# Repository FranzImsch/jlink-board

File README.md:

# Not A J-Link

Replacement board for the J-Link EDU mini that features a power supply for the target device. It allows you to directly connect a programming probe or proper 2.54mm jumper wires without any adapters and it features a contemporary USB-C port. The chip on the board was carefully removed from a genuine J-Link, so its firmware is still original.

## Partlist

| Name                | Part |
|---------------------|------------|
| C1, C2, C4, C5, C6  | 100nF 0402 |
| C8, C9              | 2.2µF 0402 |
| D1                  | LED 0603 |
| R1, R2              | 5k1 0402 |
| R3, R4              | 33Ω 0402 |
| R7                  | 10k 0402 |
| R8                  | 220Ω 0402 |
| R9 - R13            | 150Ω 0402 |
| U$2                 | TLV75533PDBVR (better: TLV75733PDBVR)        |
| IC1                 | MK22FN128VLH10 (MCU from J-Link) |
| J3                  | 6P Box Header |
| J1                  | USB-C or USB-A plug |

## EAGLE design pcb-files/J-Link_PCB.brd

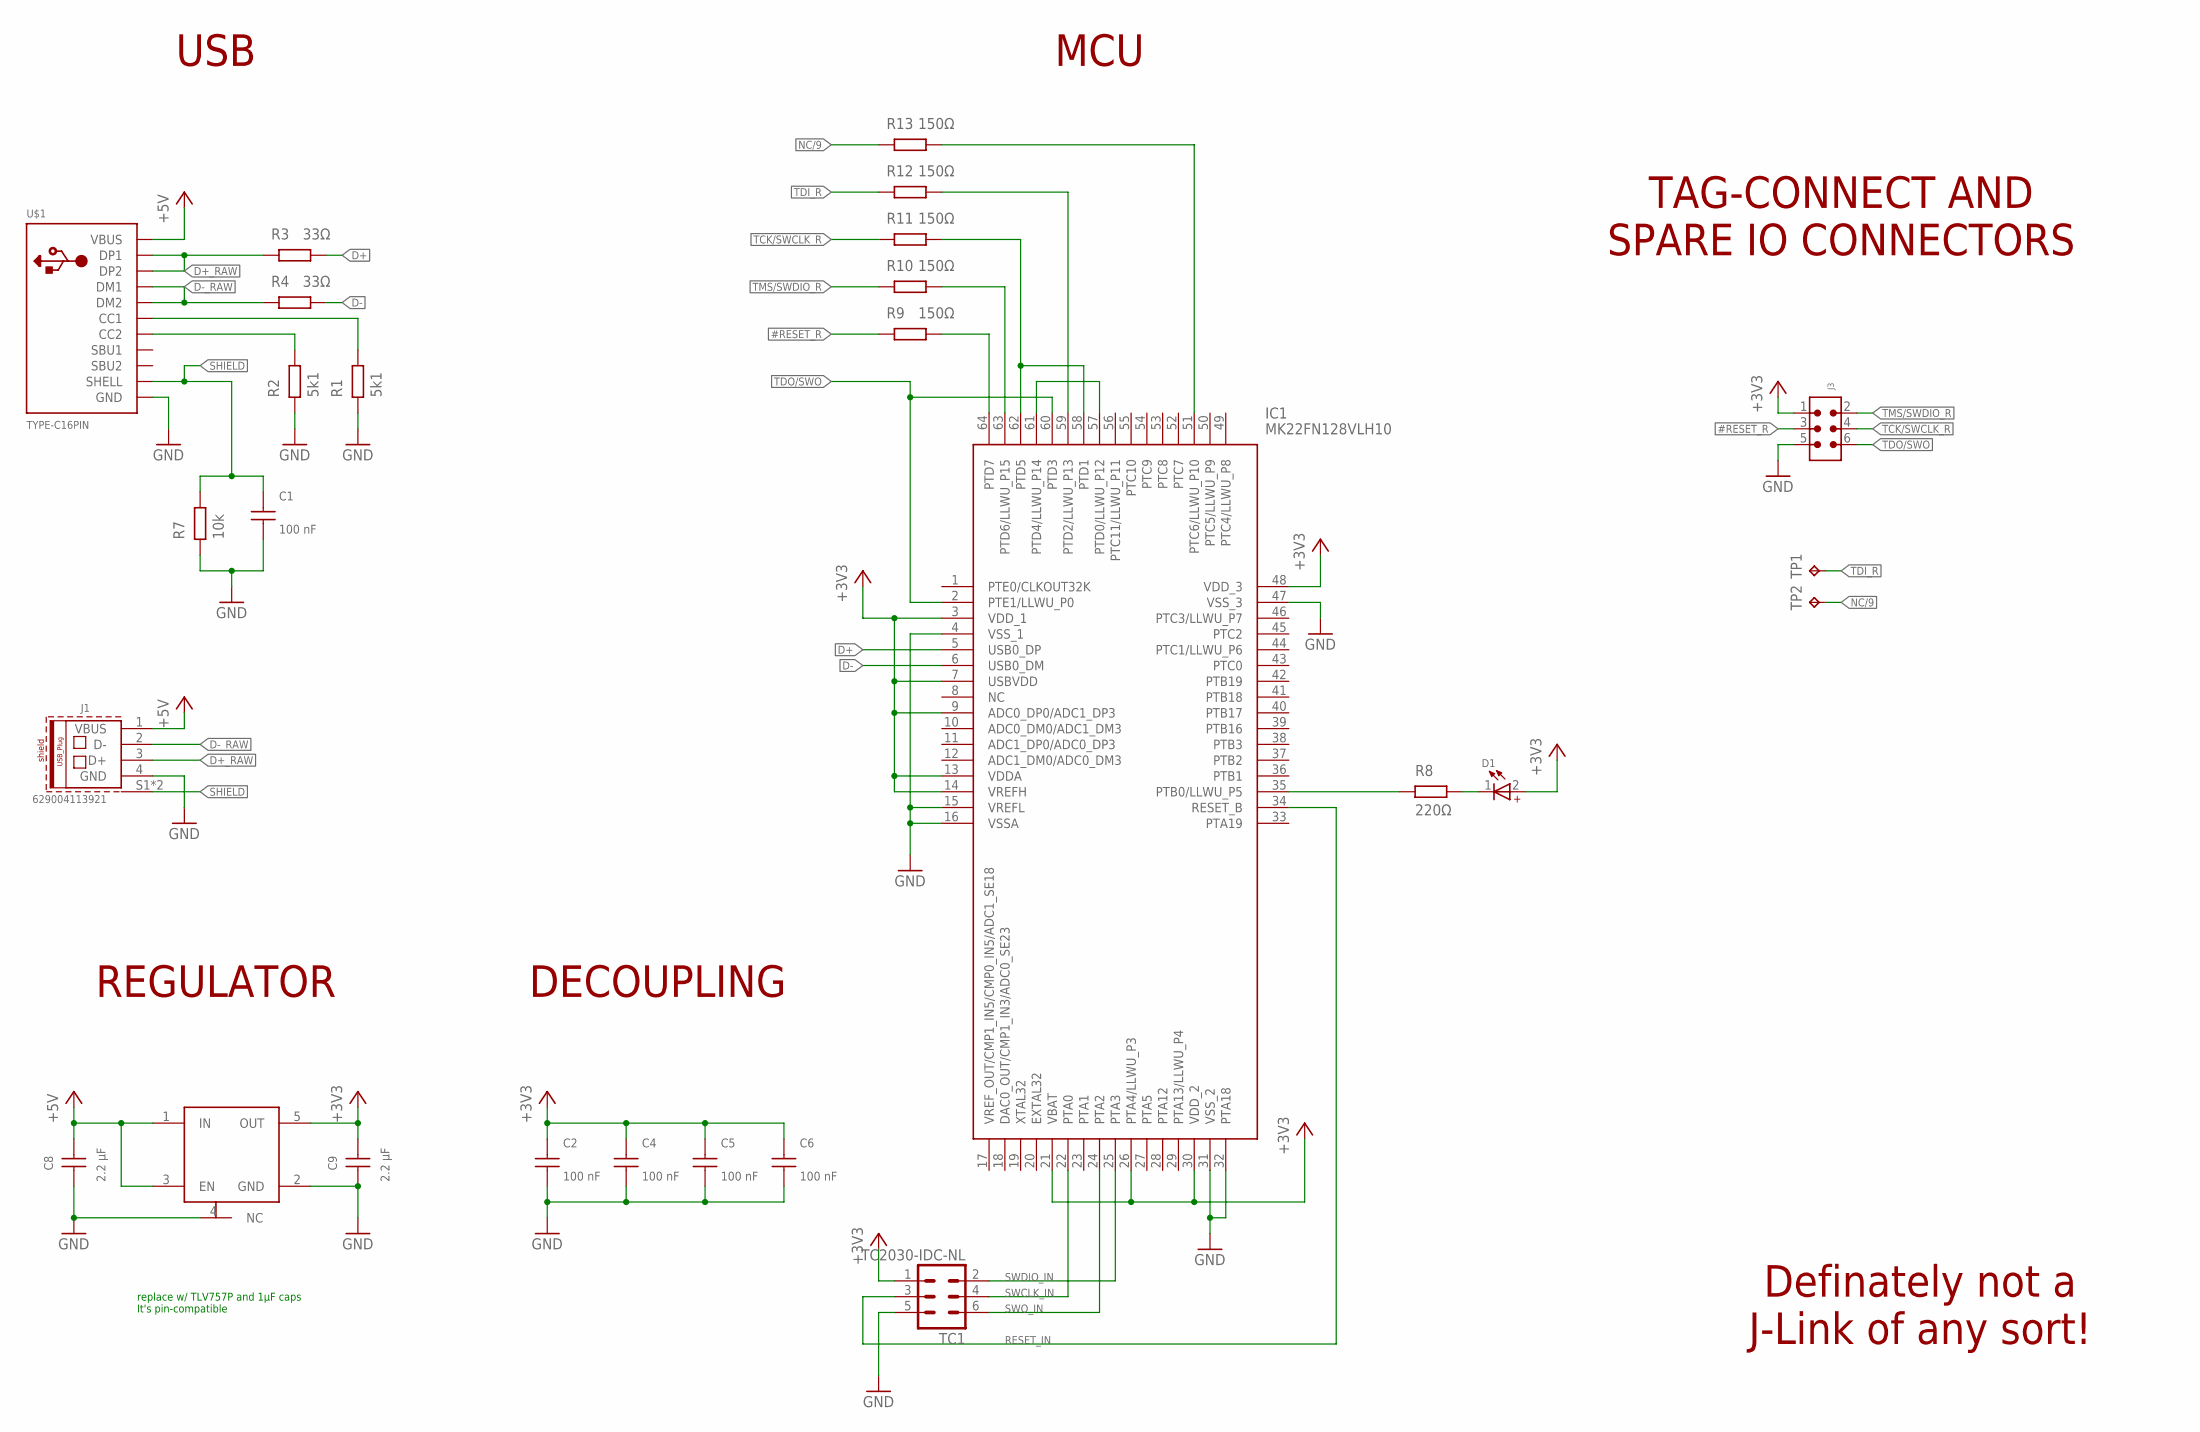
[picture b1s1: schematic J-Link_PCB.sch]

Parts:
C1, C2, C4, C5, C6: 100 nF; WCAP-CSGP_0402
C8, C9: 2.2 µF; WCAP-CSGP_0402
D1: WL-SMCW_0603_150060BS75000; WL-SMCW_0603
IC1: MK22FN128VLH10; QFP50P1200X1200X160-64N
J1: 629004113921
J3: 6120XX21621_61200621621; 61200621621
R1, R2: 5k1; WRIS-KSKE_0402
R3, R4: 33Ω; WRIS-KSKE_0402
R7: 10k; WRIS-KSKE_0402
R8: 220Ω; WRIS-KSKE_0402
R9, R10, R11, R12, R13: 150Ω; WRIS-KSKE_0402
TC1: TC2030-IDC-NL
TP1, TP2: TPTP09R; TP09R
U$1: TYPE-C16PIN
U$2: TLV75533PDBVRSOT-23-5; DBV_R-PDSO-G5

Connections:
#RESET: IC1.64 (PTD7), R9.2
#RESET_R: J3.3, R9.1
+3V3: C2.2, C4.2, C5.2, C6.2, C9.2, D1.2 (+), IC1.3 (VDD_1), IC1.7 (USBVDD), IC1.9 (ADC0_DP0/ADC1_DP3), IC1.13 (VDDA), IC1.14 (VREFH), IC1.21 (VBAT), IC1.26 (PTA4/LLWU_P3), IC1.30 (VDD_2), IC1.48 (VDD_3), J3.1, TC1.1, U$2.5 (OUT)
+5V: C8.2, J1.1 (VBUS), U$1.A4B9 (VBUS), U$1.B4A9 (VBUS), U$2.1 (IN), U$2.3 (EN)
D+: IC1.5 (USB0_DP), R3.2
D+_RAW: J1.3 (D+), R3.1, U$1.A6 (DP1), U$1.B6 (DP2)
D-: IC1.6 (USB0_DM), R4.2
D-_RAW: J1.2 (D-), R4.1, U$1.A7 (DM1), U$1.B7 (DM2)
GND: C1.1, C2.1, C4.1, C5.1, C6.1, C8.1, C9.1, IC1.4 (VSS_1), IC1.15 (VREFL), IC1.16 (VSSA), IC1.31 (VSS_2), IC1.32 (PTA18), IC1.47 (VSS_3), J1.4 (GND), J3.5, R1.1, R2.1, R7.1, TC1.5, U$1.A1B12 (GND), U$1.B1A12 (GND), U$2.2 (GND), U$2.4 (NC)
unnamed: R2.2, U$1.B5 (CC2)
unnamed: R1.2, U$1.A5 (CC1)
unnamed: IC1.59 (PTD2/LLWU_P13), R12.2
unnamed: IC1.58 (PTD1), IC1.62 (PTD5), R11.2
unnamed: IC1.57 (PTD0/LLWU_P12), IC1.61 (PTD4/LLWU_P14)
unnamed: IC1.51 (PTC6/LLWU_P10), R13.2
unnamed: IC1.35 (PTB0/LLWU_P5), R8.1
unnamed: D1.1 (-), R8.2
unnamed: IC1.63 (PTD6/LLWU_P15), R10.2
NC/9: R13.1, TP2.TP
RESET_IN: IC1.34 (RESET_B), TC1.3
SBU1: U$1.A8 (SBU1)
SBU2: U$1.B8 (SBU2)
SHIELD: C1.2, J1.S1 (SHIELD), J1.S2 (SHIELD), R7.2, U$1.SHELL1 (SHELL), U$1.SHELL2 (SHELL), U$1.SHELL3 (SHELL), U$1.SHELL4 (SHELL)
SWCLK_IN: IC1.22 (PTA0), TC1.4
SWDIO_IN: IC1.25 (PTA3), TC1.2
SWO_IN: IC1.24 (PTA2), TC1.6
TCK/SWCLK_R: J3.4, R11.1
TDI_R: R12.1, TP1.TP
TDO/SWO: IC1.2 (PTE1/LLWU_P0), IC1.60 (PTD3), J3.6
TMS/SWDIO_R: J3.2, R10.1

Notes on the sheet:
MCU
USB
REGULATOR
DECOUPLING
TAG-CONNECT AND SPARE IO CONNECTORS
Definately not a J-Link of any sort!
replace w/ TLV757P and 1µF caps It's pin-compatible

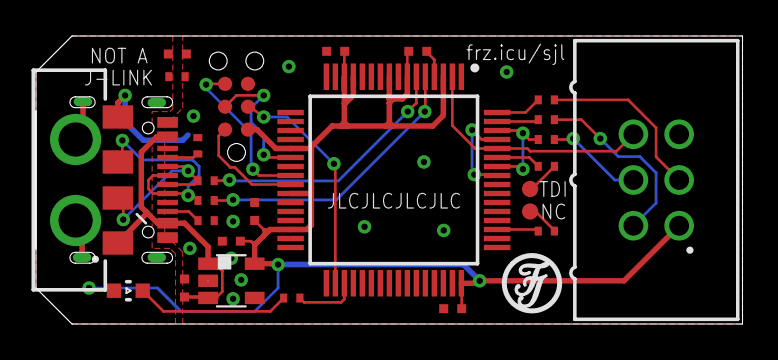
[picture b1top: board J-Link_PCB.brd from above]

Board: 2 copper layers, 39.2 x 16.0 mm, 27 parts (0 on the bottom side), 28 nets.

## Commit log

2020-10-11 initialised repo
2020-10-11 added files, fixed table in Readme
2020-10-11 poshed up readme
2020-10-12 adding assembly guide

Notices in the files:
parts and their libraries:
Wurth_Capacitors_WCAP-CSGP: Copyright: Würth Elektronik
